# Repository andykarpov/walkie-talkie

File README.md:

# Walkie-Talkie

This project is only a try to make a new pcb design to fit device into the Gainta G431 enclosure.
The original project by `blaze` is here: https://vrtp.ru/index.php?act=categories&CODE=article&article=3351

P.S. Not tested yet.

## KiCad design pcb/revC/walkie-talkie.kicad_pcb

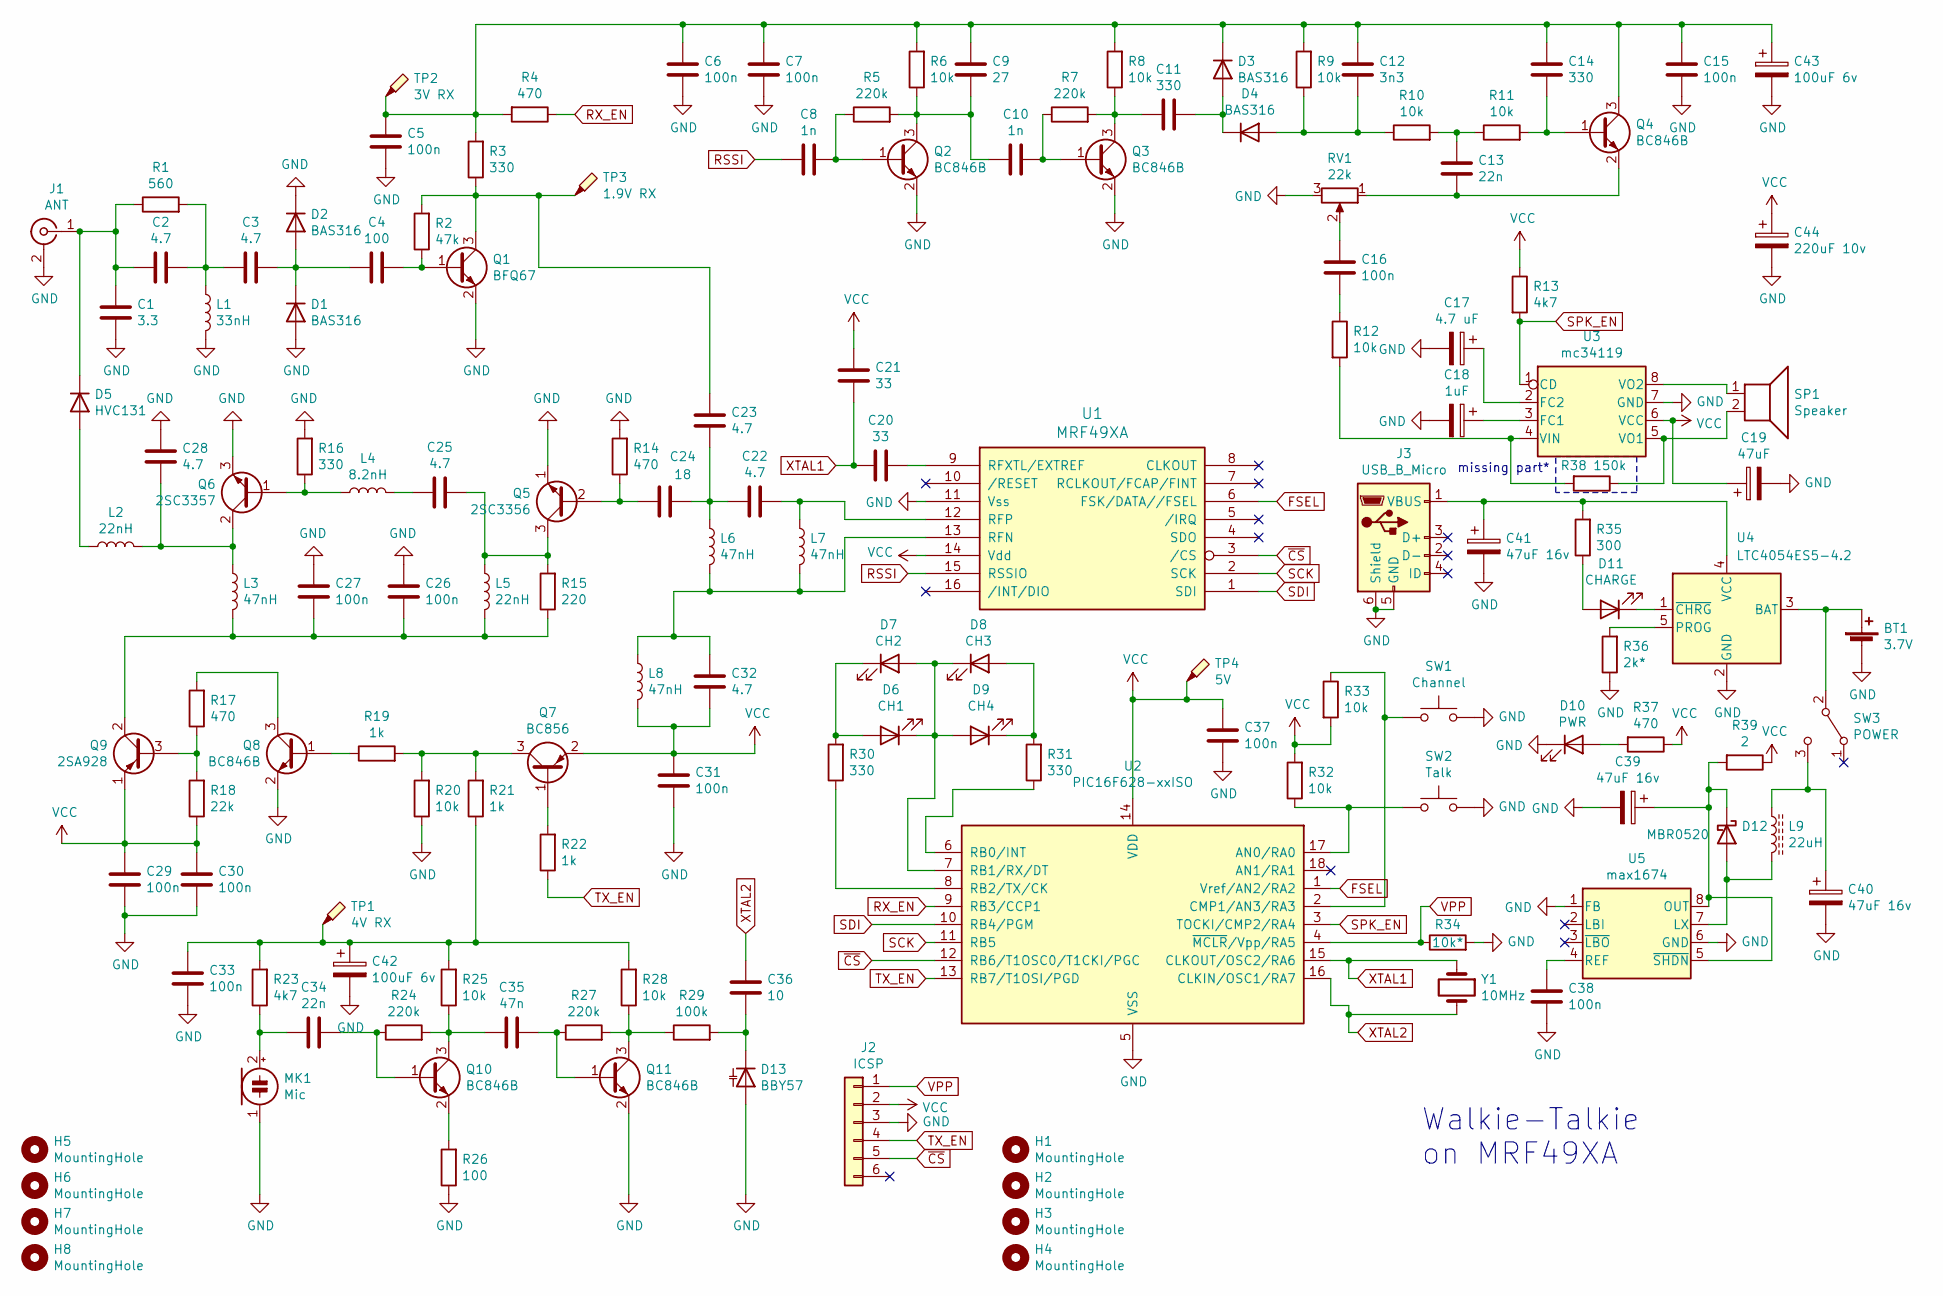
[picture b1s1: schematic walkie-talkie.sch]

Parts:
BT1: 3.7V; PinHeader_1x02_P2.54mm_Vertical
C1: 3.3; C_0805_2012Metric_Pad1.15x1.40mm_HandSolder
C2, C3, C22, C23, C25, C28, C32: 4.7; C_0805_2012Metric_Pad1.15x1.40mm_HandSolder
C4: 100; C_0805_2012Metric_Pad1.15x1.40mm_HandSolder
C5, C6, C7, C15, C16, C26, C27, C29, C30, C31, C33, C37, C38: 100n; C_0805_2012Metric_Pad1.15x1.40mm_HandSolder
C8, C10: 1n; C_0805_2012Metric_Pad1.15x1.40mm_HandSolder
C9: 27; C_0805_2012Metric_Pad1.15x1.40mm_HandSolder
C11, C14: 330; C_0805_2012Metric_Pad1.15x1.40mm_HandSolder
C12: 3n3; C_0805_2012Metric_Pad1.15x1.40mm_HandSolder
C13, C34: 22n; C_0805_2012Metric_Pad1.15x1.40mm_HandSolder
C17: 4.7 uF; CP_EIA-3528-21_Kemet-B_Pad1.50x2.35mm_HandSolder
C18: 1uF; CP_EIA-3528-21_Kemet-B_Pad1.50x2.35mm_HandSolder
C19: 47uF; CP_EIA-3528-21_Kemet-B_Pad1.50x2.35mm_HandSolder
C20, C21: 33; C_0805_2012Metric_Pad1.15x1.40mm_HandSolder
C24: 18; C_0805_2012Metric_Pad1.15x1.40mm_HandSolder
C35: 47n; C_0805_2012Metric_Pad1.15x1.40mm_HandSolder
C36: 10; C_0805_2012Metric_Pad1.15x1.40mm_HandSolder
C39, C40: 47uF 16v; CP_EIA-3528-21_Kemet-B
C41: 47uF 16v; CP_EIA-3528-21_Kemet-B_Pad1.50x2.35mm_HandSolder
C42, C43: 100uF 6v; CP_EIA-3528-21_Kemet-B
C44: 220uF 10v; CP_EIA-6032-28_Kemet-C
D1, D2, D3, D4: BAS316; D_0805_2012Metric_Castellated
D5: HVC131; D_0805_2012Metric_Castellated
D6: CH1; LED_D3.0mm
D7: CH2; LED_D3.0mm
D8: CH3; LED_D3.0mm
D9: CH4; LED_D3.0mm
D10: PWR; LED_D3.0mm
D11: CHARGE; LED_D3.0mm
D12: MBR0520; D_SMA
D13: BBY57; D_0805_2012Metric_Pad1.15x1.40mm_HandSolder
H1, H2, H3, H4: MountingHole; MountingHole_6mm
H5, H6, H7, H8: MountingHole; MountingHole_2mm
J1: ANT; SMA_Molex_73251-2200_Horizontal
J2: ICSP; PinHeader_1x06_P2.54mm_Horizontal
J3: USB_B_Micro; USB_Micro-B_Molex-105017-0001
L1: 33nH; L_0805_2012Metric_Pad1.15x1.40mm_HandSolder
L2, L5: 22nH; L_0805_2012Metric_Pad1.15x1.40mm_HandSolder
L3, L6, L7, L8: 47nH; L_0805_2012Metric_Pad1.15x1.40mm_HandSolder
L4: 8.2nH; L_0805_2012Metric_Pad1.15x1.40mm_HandSolder
L9: 22uH; L_Bourns-SRN4018
MK1: Mic; PinHeader_1x02_P2.00mm_Vertical
Q1: BFQ67; SOT-23
Q2, Q3, Q4, Q8, Q10, Q11: BC846B; SOT-23
Q5: 2SC3356; SOT-23
Q6: 2SC3357; SOT-89-3
Q7: BC856; SOT-23
Q9: 2SA928; TO-92
R1: 560; R_0805_2012Metric_Pad1.15x1.40mm_HandSolder
R2: 47k; R_0805_2012Metric_Pad1.15x1.40mm_HandSolder
R3, R16, R30, R31: 330; R_0805_2012Metric_Pad1.15x1.40mm_HandSolder
R4, R14, R17, R37: 470; R_0805_2012Metric_Pad1.15x1.40mm_HandSolder
R5, R7, R24, R27: 220k; R_0805_2012Metric_Pad1.15x1.40mm_HandSolder
R6, R8, R9, R10, R11, R12, R20, R25, R28, R32, R33: 10k; R_0805_2012Metric_Pad1.15x1.40mm_HandSolder
R13, R23: 4k7; R_0805_2012Metric_Pad1.15x1.40mm_HandSolder
R15: 220; R_0805_2012Metric_Pad1.15x1.40mm_HandSolder
R18: 22k; R_0805_2012Metric_Pad1.15x1.40mm_HandSolder
R19, R21, R22: 1k; R_0805_2012Metric_Pad1.15x1.40mm_HandSolder
R26: 100; R_0805_2012Metric_Pad1.15x1.40mm_HandSolder
R29: 100k; R_0805_2012Metric_Pad1.15x1.40mm_HandSolder
R34: 10k*; R_0805_2012Metric_Pad1.15x1.40mm_HandSolder
R35: 300; R_0805_2012Metric_Pad1.15x1.40mm_HandSolder
R36: 2k*; R_0805_2012Metric_Pad1.15x1.40mm_HandSolder
R38: 150k; R_0805_2012Metric_Pad1.15x1.40mm_HandSolder
R39: 2; R_0805_2012Metric_Pad1.15x1.40mm_HandSolder
RV1: 22k; Potentiometer_Vishay_148-149_Single_Horizontal
SP1: Speaker; PinHeader_1x02_P2.54mm_Vertical
SW1: Channel; SW_Tactile_SPST_Angled_PTS645Vx83-2LFS
SW2: Talk; SW_Tactile_SPST_Angled_PTS645Vx83-2LFS
SW3: POWER; SW_CuK_OS102011MA1QN1_SPDT_Angled
TP1: 4V RX; TestPoint_Pad_D2.0mm
TP2: 3V RX; TestPoint_Pad_D2.0mm
TP3: 1.9V RX; TestPoint_Pad_D2.0mm
TP4: 5V; TestPoint_Pad_D2.0mm
U1: MRF49XA; SSOP-16_4.4x5.2mm_P0.65mm
U2: PIC16F628-xxISO; SOP-18_7x12.5mm_P1.27mm
U3: mc34119; SO-8_3.9x4.9mm_P1.27mm
U4: LTC4054ES5-4.2; TSOT-23-5
U5: max1674; TSSOP-8_3x3mm_P0.65mm
Y1: 10MHz; Crystal_SMD_5032-2Pin_5.0x3.2mm_HandSoldering

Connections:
FSEL: U1.6 (FSK/DATA//FSEL), U2.1 (Vref/AN2/RA2)
GND: BT1.2 (-), C1.2, C5.2, C6.2, C7.2, C15.2, C17.2, C18.2, C19.2, C26.1, C27.1, C28.1, C29.2, C30.2, C31.2, C33.2, C37.2, C38.2, C39.2, C40.2, C41.2, C42.2, C43.2, C44.2, D1.2 (A), D2.1 (K), D10.1 (K), D13.2 (A), J1.2 (Ext), J2.3, J3.5 (GND), J3.6 (Shield), L1.2, MK1.1 (-), Q1.2 (E), Q2.2 (E), Q3.2 (E), Q5.1 (E), Q6.3 (E), Q8.2 (E), Q11.2 (E), R14.2, R16.2, R20.1, R26.1, R34.2, R36.1, RV1.3, SW1.2, SW2.2, U1.11 (Vss), U2.5 (VSS), U3.7 (GND), U4.2 (GND), U5.1 (FB), U5.6 (GND)
unnamed: BT1.1 (+), SW3.2 (B), U4.3 (BAT)
unnamed: C1.1, C2.1, D5.1 (K), J1.1 (In), R1.1
unnamed: C2.2, C3.1, L1.1, R1.2
unnamed: C3.2, C4.1, D1.1 (K), D2.2 (A)
unnamed: C4.2, Q1.1 (B), R2.1
unnamed: C8.2, Q2.1 (B), R5.1
unnamed: C9.2, C10.1, Q2.3 (C), R5.2, R6.1
unnamed: C10.2, Q3.1 (B), R7.1
unnamed: C11.1, Q3.3 (C), R7.2, R8.1
unnamed: C11.2, D3.2 (A), D4.1 (K)
unnamed: C5.1, C6.1, C7.1, C9.1, C12.1, C14.1, C15.1, C43.1, D3.1 (K), Q4.3 (C), R3.2, R4.2, R6.2, R8.2, R9.2, TP2.1
unnamed: C12.2, D4.2 (A), R9.1, R10.1
unnamed: C13.1, R10.2, R11.1
unnamed: C13.2, Q4.2 (E), RV1.1
unnamed: C14.2, Q4.1 (B), R11.2
unnamed: C16.1, RV1.2
unnamed: C16.2, R12.1
unnamed: C17.1, U3.2 (FC2)
unnamed: C18.1, U3.3 (FC1)
unnamed: C20.2, U1.9 (RFXTL/EXTREF)
unnamed: C22.1, C23.2, C24.2, L6.1
unnamed: C22.2, L7.1, U1.12 (RFP)
unnamed: C23.1, Q1.3 (C), R2.2, R3.1, TP3.1
unnamed: C24.1, Q5.2 (B), R14.1
unnamed: C25.1, L4.2
unnamed: C25.2, L5.1, Q5.3 (C), R15.2
unnamed: C26.2, C27.2, L3.2, L5.2, Q9.2 (C), R15.1
unnamed: C28.2, L2.2, L3.1, Q6.2 (C)
unnamed: C32.1, L6.2, L7.2, L8.1, U1.13 (RFN)
unnamed: C33.1, C42.1, R21.1, R23.2, R25.2, R28.2, TP1.1
unnamed: C34.1, MK1.2 (+), R23.1
unnamed: C34.2, Q10.1 (B), R24.1
unnamed: C35.1, Q10.3 (C), R24.2, R25.1
unnamed: C35.2, Q11.1 (B), R27.1
unnamed: C36.2, D13.1 (K), R29.2
unnamed: C38.1, U5.4 (REF)
unnamed: C39.1, D12.1 (K), R39.2, U5.5 (~SHDN), U5.8 (OUT)
unnamed: C40.1, L9.1, SW3.3 (C)
unnamed: C41.1, J3.1 (VBUS), R35.2, U4.4 (VCC)
unnamed: D5.2 (A), L2.1
unnamed: D6.1 (K), D7.2 (A), D8.1 (K), D9.2 (A), U2.7 (RB1/RX/DT)
unnamed: D6.2 (A), D7.1 (K), R30.2
unnamed: D8.2 (A), D9.1 (K), R31.2
unnamed: D10.2 (A), R37.2
unnamed: D11.1 (K), U4.1 (~CHRG)
unnamed: D11.2 (A), R35.1
unnamed: D12.2 (A), L9.2, U5.7 (LX)
unnamed: L4.1, Q6.1 (B), R16.1
unnamed: Q7.1 (B), R22.2
unnamed: Q7.3 (C), R19.2, R20.2, R21.2
unnamed: Q8.1 (B), R19.1
unnamed: Q8.3 (C), R17.2
unnamed: Q9.3 (B), R17.1, R18.2
unnamed: Q10.2 (E), R26.2
unnamed: Q11.3 (C), R27.2, R28.1, R29.1
unnamed: R12.2, R38.2, U3.4 (VIN)
unnamed: R30.1, U2.8 (RB2/TX/CK)
unnamed: R31.1, U2.6 (RB0/INT)
unnamed: R32.1, SW2.1, U2.17 (AN0/RA0)
unnamed: R33.1, SW1.1, U2.2 (CMP1/AN3/RA3)
unnamed: R36.2, U4.5 (PROG)
unnamed: R38.1, SP1.2, U3.5 (VO1)
unnamed: SP1.1, U3.8 (VO2)
RSSI: C8.1, U1.15 (RSSIO)
RX_EN: R4.1, U2.9 (RB3/CCP1)
SCK: U1.2 (SCK), U2.11 (RB5)
SDI: U1.1 (SDI), U2.10 (RB4/PGM)
SPK_EN: R13.2, U2.3 (TOCKI/CMP2/RA4), U3.1 (CD)
TX_EN: J2.4, R22.1, U2.13 (RB7/T1OSI/PGD)
VCC: C19.1, C21.1, C29.1, C30.1, C31.1, C32.2, C37.1, C44.1, J2.2, L8.2, Q7.2 (E), Q9.1 (E), R13.1, R18.1, R32.2, R33.2, R37.1, R39.1, TP4.1, U1.14 (Vdd), U2.14 (VDD), U3.6 (VCC)
VPP: J2.1, R34.1, U2.4 (~MCLR~/Vpp/RA5)
XTAL1: C20.1, C21.2, U2.15 (CLKOUT/OSC2/RA6), Y1.1
XTAL2: C36.1, U2.16 (CLKIN/OSC1/RA7), Y1.2
~CS: J2.5, U1.3 (/CS), U2.12 (RB6/T1OSC0/T1CKI/PGC)

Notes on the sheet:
Walkie-Talkie on MRF49XA
missing part*

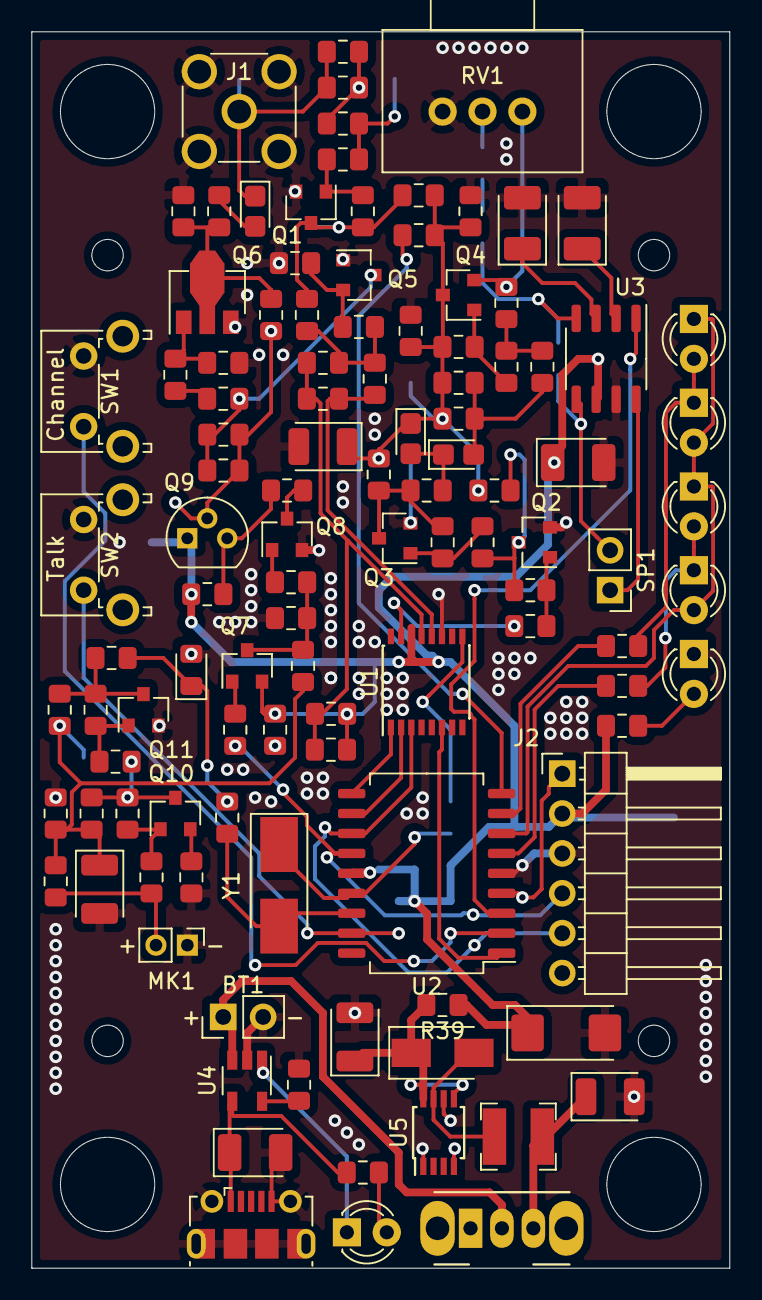
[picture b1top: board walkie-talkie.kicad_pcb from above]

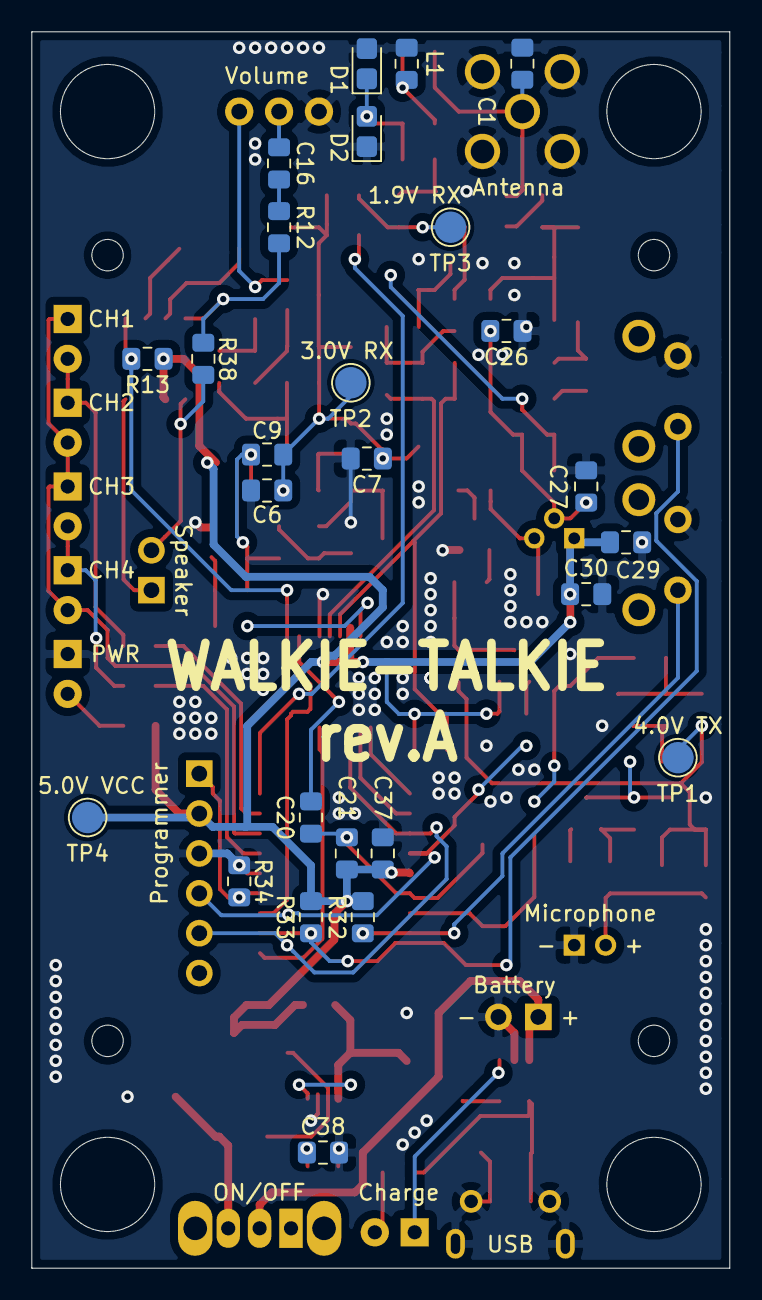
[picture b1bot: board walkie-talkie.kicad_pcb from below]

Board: 2 copper layers, 44.5 x 78.7 mm, 144 parts (26 on the bottom side), 76 nets.

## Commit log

2020-05-02 Delete .~lock.walkie-talkie-bom-revA.ods#
    temp file removal
2020-05-02 Fixed bugs in rev.A
2020-07-15 Rev.C
